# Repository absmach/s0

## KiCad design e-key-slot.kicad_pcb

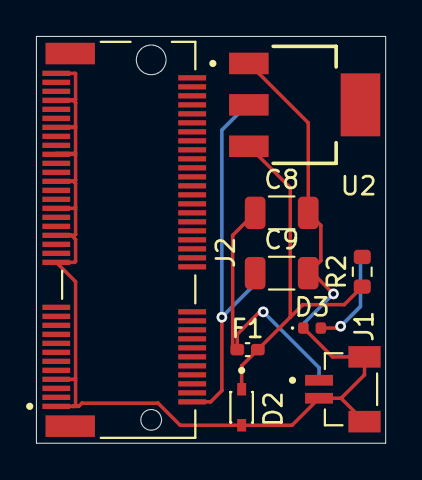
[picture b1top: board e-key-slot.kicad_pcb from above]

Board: 2 copper layers, 19.4 x 22.6 mm, 9 parts (0 on the bottom side), 5 nets.

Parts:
C8, C9: 10uF; C_1206_3216Metric
D2: BZT52C12S; DIO_BZT52C12S
D3: LED; LED_0402_1005Metric
F1: Fuse; Fuse_0402_1005Metric_Pad0.77x0.64mm_HandSolder
J1: BM02B-SRSS-TB_LF__SN_; JST_BM02B-SRSS-TB_LF__SN_
J2: MDT420E03002; AMPHENOL_MDT420E03002
R2: 100; R_0603_1608Metric
U2: AZ1117IH-3.3TRG1; SOT230P700X185-4N

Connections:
+3V3: C9.1, J2.2, U2.2 (OUTPUT)
GND: C8.2, C9.2, D2.A, D3.1 (K), J1.2, J1.S1 (SHIELD), J1.S2 (SHIELD), J2.1, J2.7, J2.33, J2.39, J2.45, J2.51, J2.57, J2.63, J2.69, J2.75, U2.1 (GND)
INPUT: D2.C, F1.2, R2.1, U2.3 (INPUT)
unnamed: D3.2 (A), R2.2
VIN: C8.1, F1.1, J1.1

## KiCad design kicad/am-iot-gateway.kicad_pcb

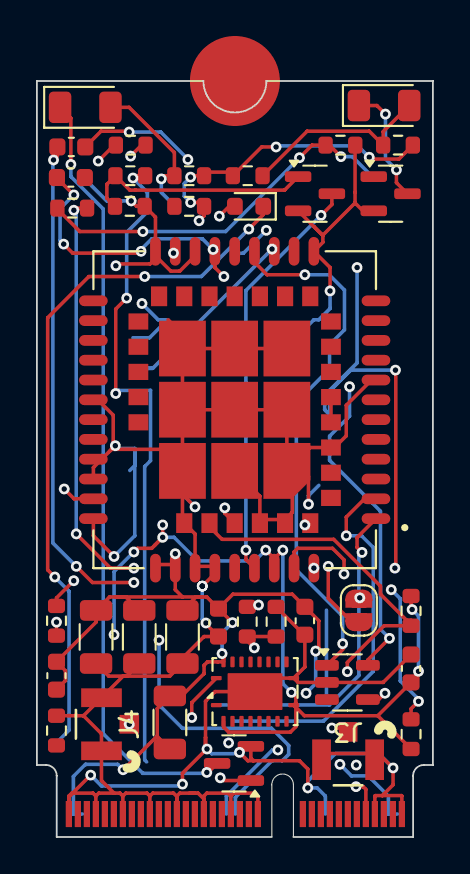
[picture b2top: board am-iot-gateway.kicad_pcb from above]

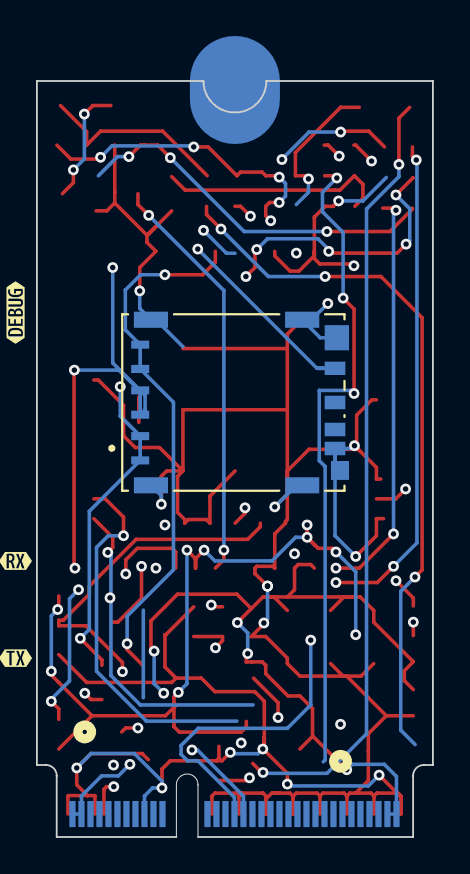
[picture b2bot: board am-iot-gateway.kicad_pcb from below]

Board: 4 copper layers, 22.0 x 42.0 mm, 42 parts (4 on the bottom side), 31 nets.

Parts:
C1, C13, C14, C15: 100uF; C_1206_3216Metric
C2, C16: 1uF; C_0603_1608Metric
C7: 33pF; C_0603_1608Metric
C10, C11, C12: 0.1uF; C_0603_1608Metric
D1: LED; LED_0603_1608Metric
D2, D4: LED; LED_1206_3216Metric
D3: ESDA6V1SC5; SOT-23-5
J1: Bus_M.2_Socket_E; 2242-key-E
J3: GNSS Antenna; CONN1_CONUFL_TEC
J4: RF Antenna; CONN1_CONUFL_TEC
J5: NSIM-5-B; CUI_NSIM-5-B
JP1: SolderJumper_2_Open; SolderJumper-2_P1.3mm_Open_RoundedPad1.0x1.5mm
Q1, Q2, Q3: SS8050; SOT-23
R1, R3, R4, R11, R12: 100; R_0603_1608Metric
R5: 10K; R_0603_1608Metric
R6, R13, R15: 4.7K; R_0603_1608Metric
R7: 0K; R_0603_1608Metric
R8, R10: 1K; R_0603_1608Metric
R9, R14, R16: 47K; R_0603_1608Metric
U2: SIM7080G; XCVR_SIM7080G
U3: TXB0108RGY; Texas_RGY_R-PVQFN-N20_EP2.05x3.05mm
kibuzzard-6729E0B5: G***; kibuzzard-6729E0B5
kibuzzard-6729E0D0: G***; kibuzzard-6729E0D0
kibuzzard-6729E0DB: G***; kibuzzard-6729E0DB

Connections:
+1V8: C10.1, R3.1, R4.1, R5.2, R8.1, R10.1, R11.1, R12.1, U2.40 (VDD_EXT), U3.2 (V_{CCA}), U3.10 (OE)
+3V3: C1.1, C1.2, C2.1, C2.2, C11.1, C13.1, C14.1, C15.1, C16.1, D1.2 (A), J1.2 (3.3V), J1.4 (3.3V), J1.72 (3.3V), J1.74 (3.3V), U2.34 (VBAT), U2.35 (VBAT__1), U3.19 (V_{CCB})
GND: C10.2, C11.2, C12.2, C13.2, C14.2, C15.2, C16.2, D3.2 (A), J1.1 (GND), J1.7 (GND), J1.18 (GND), J1.33 (GND), J1.39 (GND), J1.45 (GND), J1.51 (GND), J1.57 (GND), J1.63 (GND), J1.69 (GND), J1.75 (GND), J3.2, J3.3, J4.2, J4.3, J5.C5 (GND), J5.G1 (COVER_GND), J5.G2 (COVER_GND__1), J5.G3 (COVER_GND__2), J5.G4 (COVER_GND__3), J5.G5 (COVER_GND__4), J5.G6 (COVER_GND__5), Q1.2 (E), Q2.2 (E), Q3.2 (E), R1.2, R9.1, R14.1, R16.1, U2.8 (GND), U2.13 (GND__1), U2.19 (GND__2), U2.21 (GND__3), U2.27 (GND__4), U2.30 (GND__5), U2.31 (GND__6), U2.33 (GND__7), U2.36 (GND__8), U2.37 (GND__9), U2.45 (GND__10), U2.63 (GND__11), U2.66 (GND__12), U2.67 (GND__13), U2.69 (GND__14), U2.70 (GND__15), U2.71 (GND__16), U2.72 (GND__17), U2.73 (GND__18), U2.74 (GND__19), U2.75 (GND__20), U2.76 (GND__21), U2.77 (GND__22), U3.11 (GND), U3.21 (GND)
GNSS_ANT: C7.1, U2.68 (GNSS_ANT)
NETLIGHT: R6.2, U2.41 (NETLIGHT)
unnamed: C7.2, J3.1
unnamed: D1.1 (K), R1.1
unnamed: D2.2 (A), R3.2, R4.2
unnamed: D2.1 (K), Q1.3 (C)
unnamed: D4.2 (A), R11.2, R12.2
unnamed: D4.1 (K), Q2.3 (C)
unnamed: J4.1, R7.1
unnamed: JP1.1 (A), R5.1
unnamed: JP1.2 (B), U2.20 (USB_BOOT)
unnamed: Q1.1 (B), R6.1, R9.2
unnamed: Q2.1 (B), R13.1, R14.2
unnamed: Q3.1 (B), R15.1, R16.2
PWR_KEY: Q3.3 (C), U2.39 (PWRKEY)
RF_ANT: R7.2, U2.32 (RF_ANT)
SIM7080G_PWR: J1.13 (SDIO_DATA0), R15.2
SIM7080G_RXD: J1.11 (SDIO_CMD), U3.18 (B2)
SIM7080G_SCL: J1.38 (VENDOR_DEFINED), R8.2, U2.65 (I2C_SCL)
SIM7080G_SDA: J1.40 (VENDOR_DEFINED), R10.2, U2.64 (I2C_SDA)
SIM7080G_TXD: J1.9 (SDIO_CLK), U3.20 (B1)
SIM_CLK: D3.1 (K), J5.C3_1 (CLK), J5.C3_2 (CLK__1), U2.16 (SIM_CLK)
SIM_DATA: D3.3 (K), J5.C7 (I/O), U2.15 (SIM_DATA)
SIM_RST: D3.4 (K), J5.C2_1 (RST), J5.C2_2 (RST__1), U2.17 (SIM_RST)
SIM_VDD: C12.1, D3.5 (K), J5.C1_1 (VCC), J5.C1_2 (VCC__1), U2.18 (SIM_VDD)
STATUS: R13.2, U2.42 (STATUS)
UART1_RXD: U2.2 (UART1_RXD), U3.3 (A2)
UART1_TXD: U2.1 (UART1_TXD), U3.1 (A1)

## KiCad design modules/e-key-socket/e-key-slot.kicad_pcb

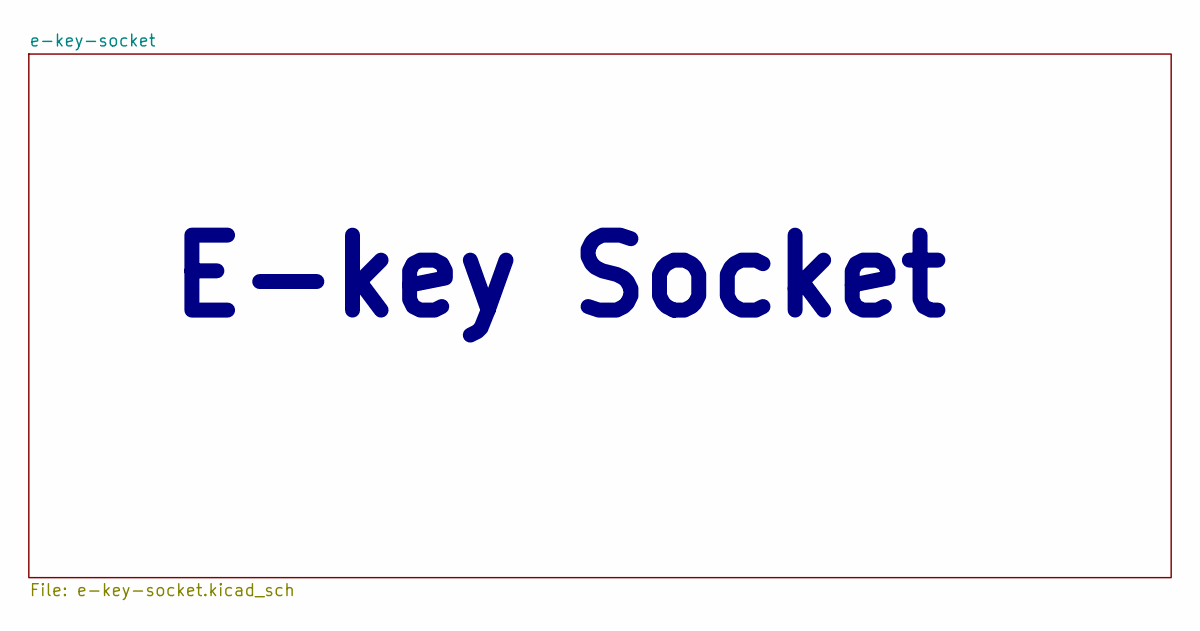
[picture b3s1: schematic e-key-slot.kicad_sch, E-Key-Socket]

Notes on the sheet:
E-key Socket

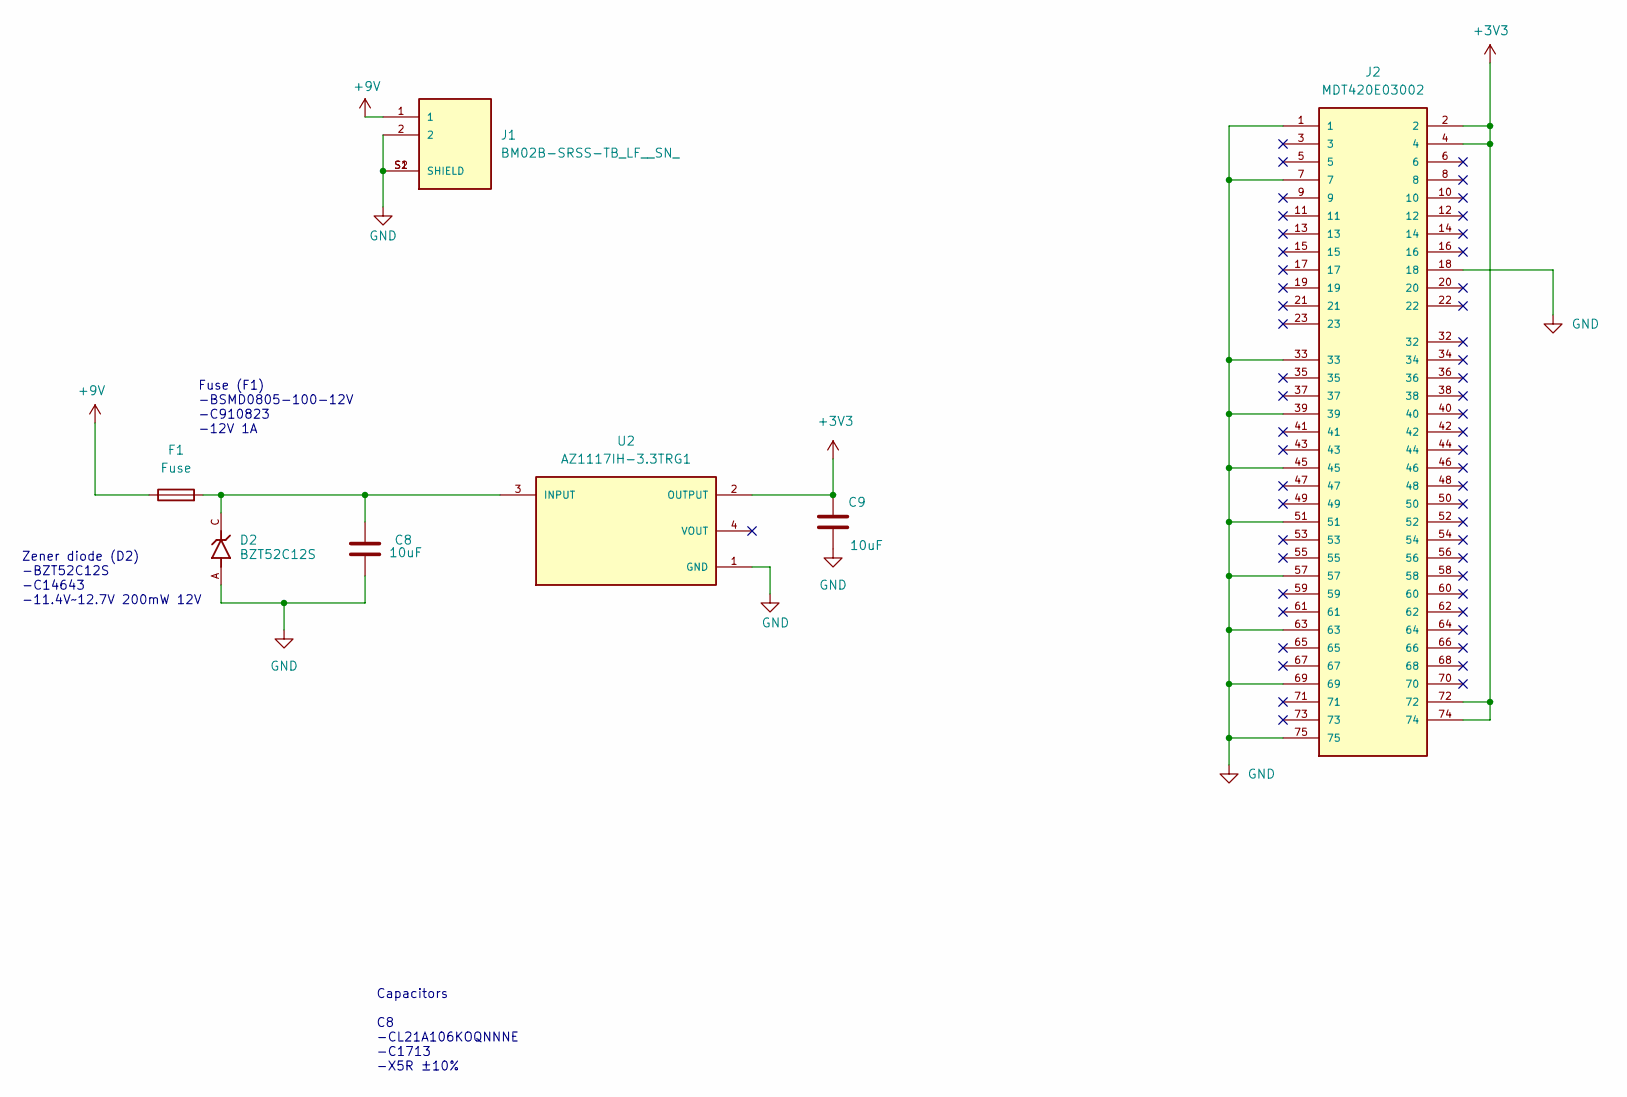
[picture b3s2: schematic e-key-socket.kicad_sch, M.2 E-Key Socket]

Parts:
C8, C9: 10uF; C_1206_3216Metric
D2: BZT52C12S; DIO_BZT52C12S; PARTREV H2212
F1: Fuse; Fuse_0402_1005Metric_Pad0.77x0.64mm_HandSolder
J1: BM02B-SRSS-TB_LF__SN_; JST_BM02B-SRSS-TB_LF__SN_; PARTREV N/A
J2: MDT420E03002; AMPHENOL_MDT420E03002; PARTREV 3
U2: AZ1117IH-3.3TRG1; SOT230P700X185-4N; PARTREV 2-2

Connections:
+3V3: C9.1, J2.2, J2.4, J2.72, J2.74, U2.2 (OUTPUT)
+9V: F1.1, J1.1
GND: C8.2, C9.2, D2.A, J1.2, J1.S1 (SHIELD), J1.S2 (SHIELD), J2.1, J2.7, J2.18, J2.33, J2.39, J2.45, J2.51, J2.57, J2.63, J2.69, J2.75, U2.1 (GND)
unnamed: C8.1, D2.C, F1.2, U2.3 (INPUT)

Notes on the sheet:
Capacitors C8 -CL21A106KOQNNNE -C1713 -X5R ±10%
Fuse (F1) -BSMD0805-100-12V -C910823 -12V 1A
Zener diode (D2) -BZT52C12S -C14643 -11.4V~12.7V 200mW 12V

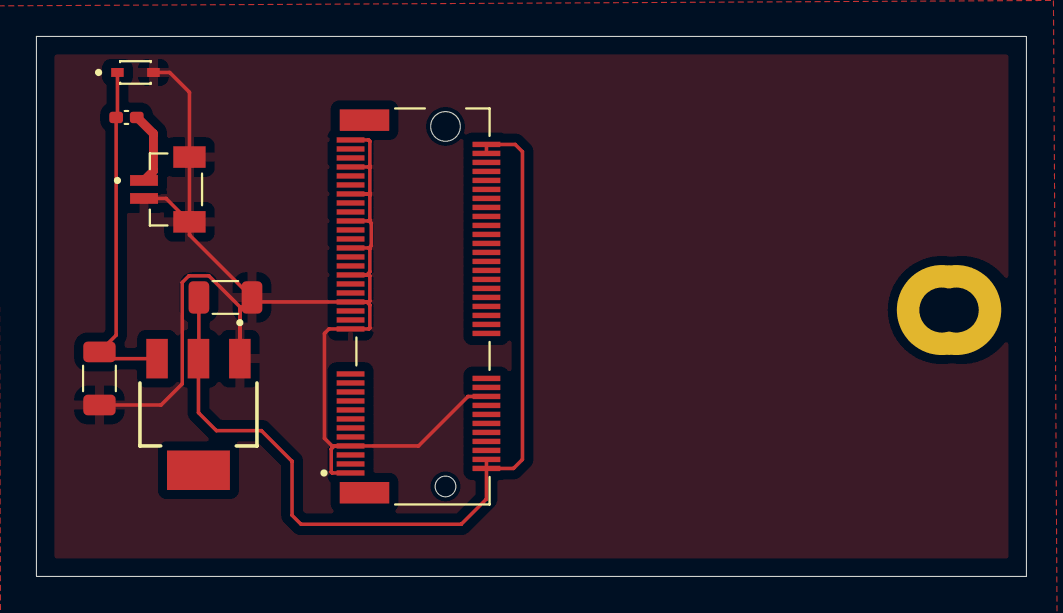
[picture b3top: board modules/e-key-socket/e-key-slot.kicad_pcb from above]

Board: 2 copper layers, 55.0 x 30.0 mm, 7 parts (0 on the bottom side), 4 nets.
